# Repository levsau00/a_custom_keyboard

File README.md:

# a_custom_keyboard
an attempt at designing/creating a split ortholinear column staggered mechanical keyboard based on a keyboard designed by Christian Selig

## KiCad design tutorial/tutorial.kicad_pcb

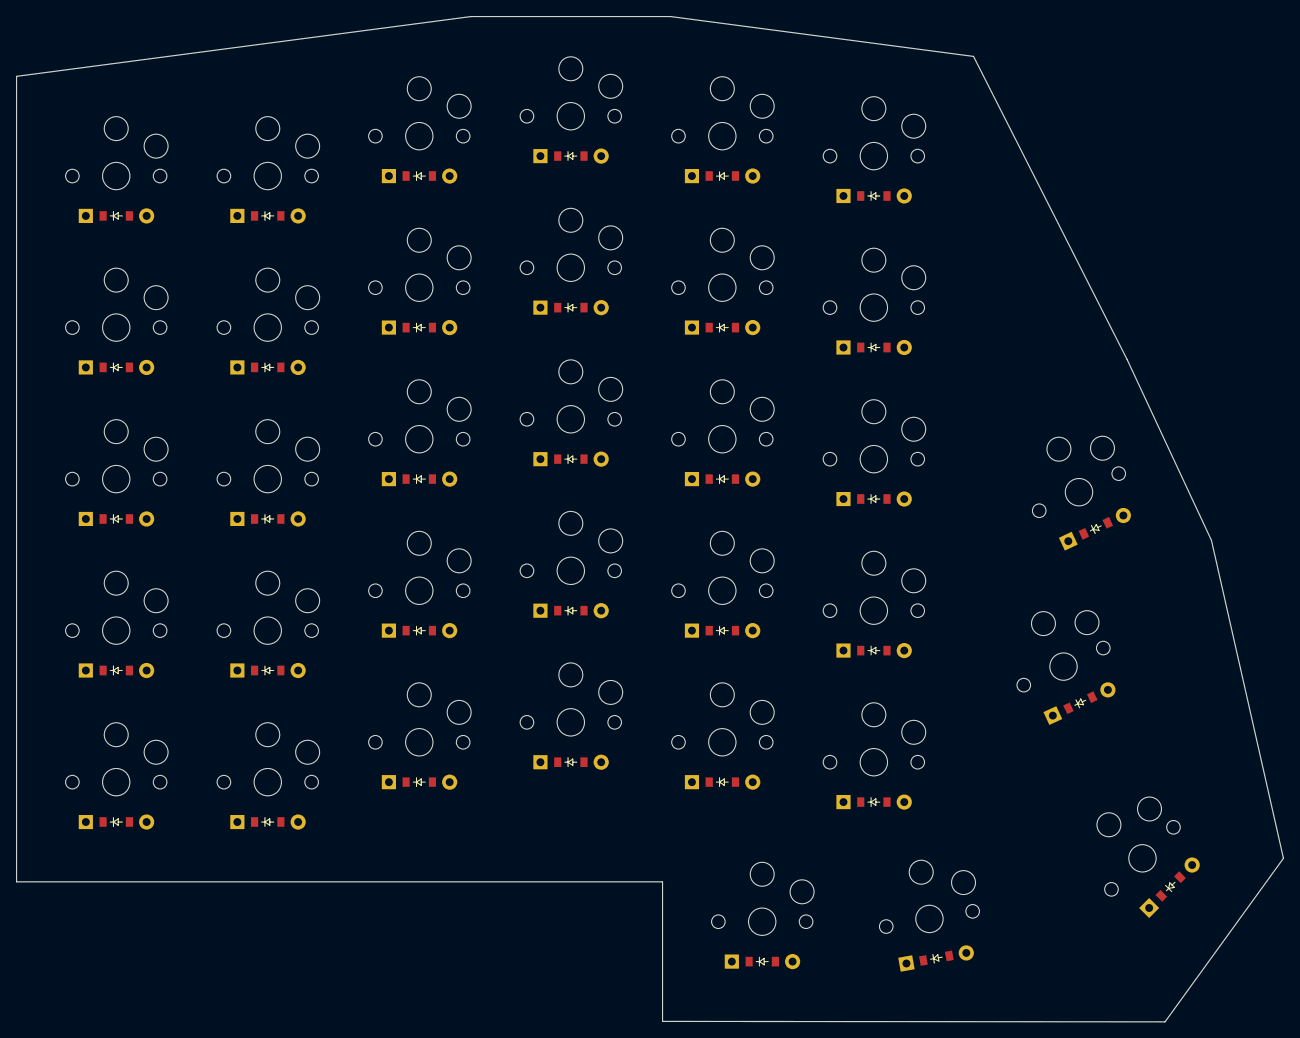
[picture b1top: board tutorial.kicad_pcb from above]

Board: 2 copper layers, 158.9 x 126.1 mm, 70 parts (0 on the bottom side), 35 nets, no tracks yet.

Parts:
D1, D2, D3, D4, D5, D6, D7, D8, D9, D10, D11, D12, D13, D14, D15, D16, D17, D18, D19, D20, D21, D22, D23, D24, D25, D26, D27, D28, D29, D30, D31, D32, D33, D34, D35: ComboDiode
S1, S2, S3, S4, S5, S6, S7, S8, S9, S10, S11, S12, S13, S14, S15, S16, S17, S18, S19, S20, S21, S22, S23, S24, S25, S26, S27, S28, S29, S30, S31, S32, S33, S34, S35: PG1350

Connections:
farleft_alpha_bot: D2.2, S2.2
farleft_alpha_mid: D3.2, S3.2
farleft_alpha_top: D4.2, S4.2
farleft_mod: D1.2, S1.2
farleft_number: D5.2, S5.2
farright_alpha_bot: D27.2, S27.2
farright_alpha_mid: D28.2, S28.2
farright_alpha_top: D29.2, S29.2
farright_mod: D26.2, S26.2
farright_number: D30.2, S30.2
index_alpha_bot: D22.2, S22.2
index_alpha_mid: D23.2, S23.2
index_alpha_top: D24.2, S24.2
index_mod: D21.2, S21.2
index_number: D25.2, S25.2
middle_alpha_bot: D17.2, S17.2
middle_alpha_mid: D18.2, S18.2
middle_alpha_top: D19.2, S19.2
middle_mod: D16.2, S16.2
middle_number: D20.2, S20.2
pinky_alpha_bot: D7.2, S7.2
pinky_alpha_mid: D8.2, S8.2
pinky_alpha_top: D9.2, S9.2
pinky_mod: D6.2, S6.2
pinky_number: D10.2, S10.2
ring_alpha_bot: D12.2, S12.2
ring_alpha_mid: D13.2, S13.2
ring_alpha_top: D14.2, S14.2
ring_mod: D11.2, S11.2
ring_number: D15.2, S15.2
thumbC_bottom: D32.2, S32.2
thumbL_bottom: D31.2, S31.2
thumbR_bottom: D33.2, S33.2
thumbR_middle: D34.2, S34.2
thumbR_top: D35.2, S35.2

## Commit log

2024-08-10 add basic ergogen config
2024-08-10 add pcb section
